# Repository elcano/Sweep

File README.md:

# Sweep
Lidar data collection from Scanse Sweep

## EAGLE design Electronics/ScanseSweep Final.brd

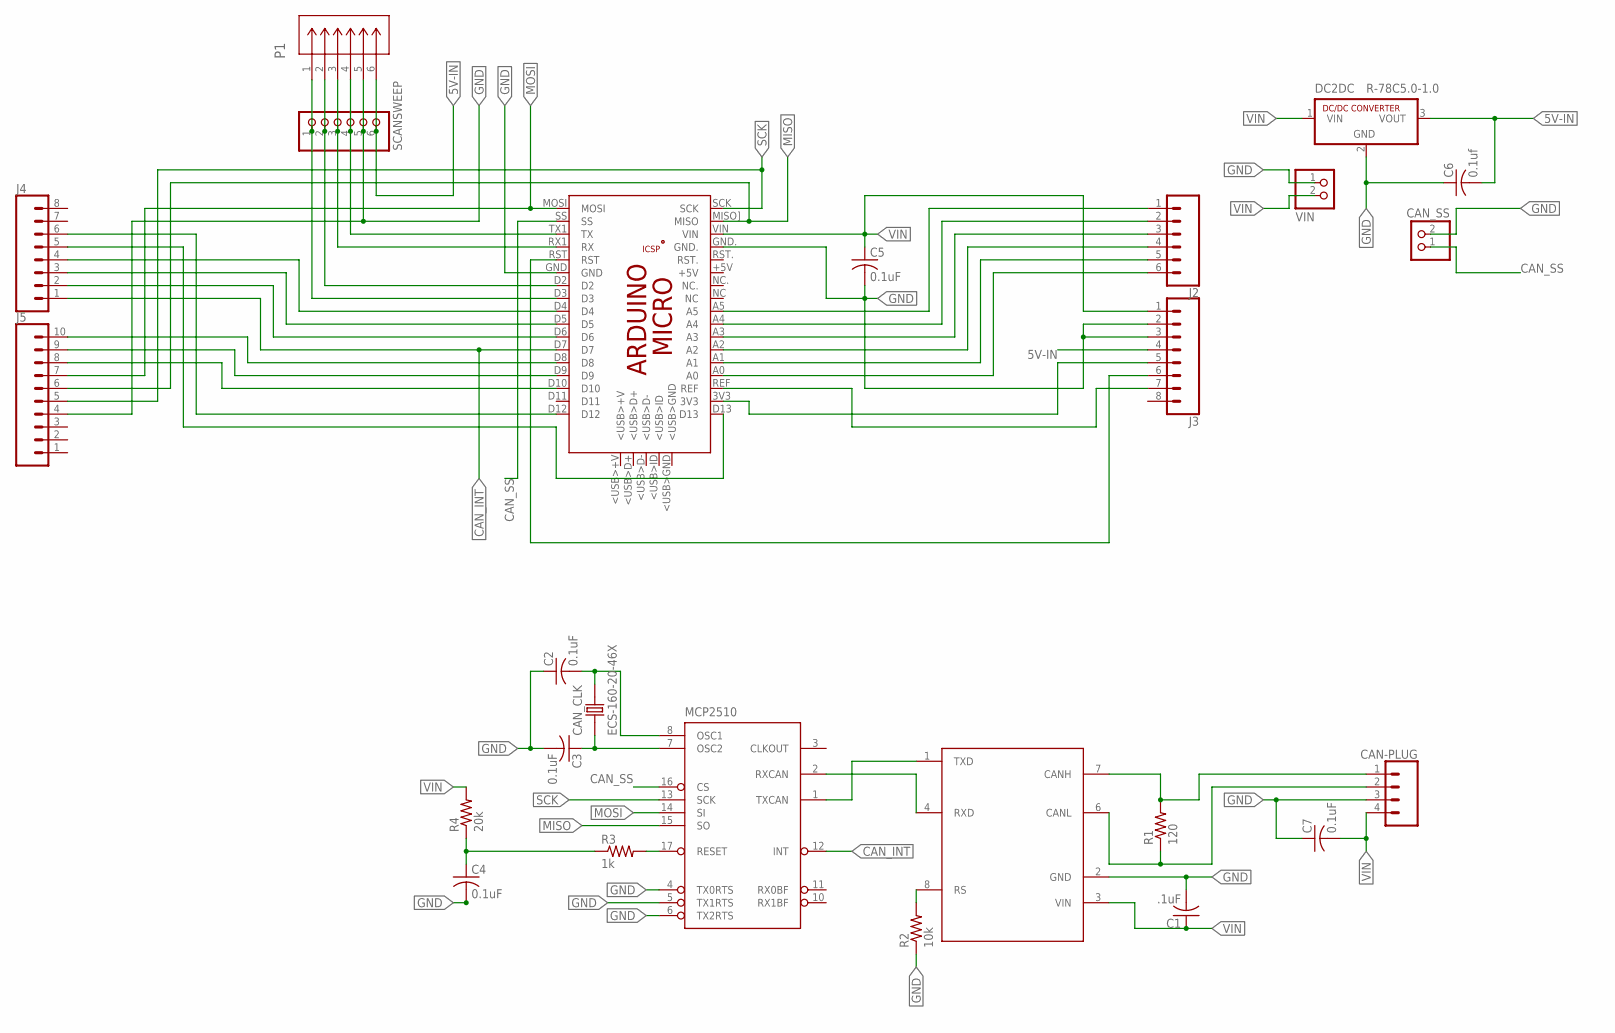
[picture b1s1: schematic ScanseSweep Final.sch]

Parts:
C1: .1uF; C025-024X044
C2, C3, C4, C5, C7: 0.1uF; C025-024X044
C6: 0.1uf; C025-024X044
CAN_CLK: ECS-160-20-46X; XTAL_ECS-160-20-46X
CAN_SS_TEST: CAN_SS; 1X02
DC2DC: R-78C5.0-1.0; SIP3
J1: CAN-PLUG; SCREWTERMINAL-3.5MM-4
J2: CONN_06SILK_FEMALE_PTH; 1X06
J3, J4: CONN_08"; 1X08
J5: CONN_10"; 1X10
MCP2510: MCP2510P; DIL18
MCP2551: MCP2551MCP2551; DIL08
P1: S6B-ZR(LF)(SN); S6B-ZR
PCB2: ARDUINO_MICRO
R1: 120; 0204/5
R2: 10k; 0204/5
R3: 1k; 0204/5
R4: 20k; 0204/5
SCANSESWEEP: SCANSWEEP; 1X06
VIN_TEST: VIN; 1X02

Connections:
3.3V: J3.5, PCB2.3V3
5V-IN: C6.2, DC2DC.3 (VOUT), J3.4, P1.6, SCANSESWEEP.6
A0: J2.6, PCB2.A0
A1: J2.5, PCB2.A1
A2: J2.4, PCB2.A2
A3: J2.3, PCB2.A3
A4: J2.2, PCB2.A4
A5: J2.1, PCB2.A5
CANH: J1.1, MCP2551.7 (CANH), R1.2
CANL: J1.2, MCP2551.6 (CANL), R1.1
CAN_INT: J4.1, MCP2510.12 (INT), PCB2.D7
CAN_SS: CAN_SS_TEST.1, MCP2510.16 (CS), PCB2.SS
D2: P1.2, PCB2.D2, SCANSESWEEP.2
D3: P1.1, PCB2.D3, SCANSESWEEP.1
D4: J4.4, PCB2.D4
D5: J4.3, PCB2.D5
D6: J4.2, PCB2.D6
D8: J5.10, PCB2.D8
D9: J5.9, PCB2.D9
D10: J5.8, PCB2.D10
D12: J4.6, PCB2.D12
D13: J4.5, PCB2.D13
GND: C1.2, C2.1, C3.2, C4.2, C5.2, C6.1, C7.1, CAN_SS_TEST.2, DC2DC.2 (GND), J1.3, J3.2, J3.3, J5.4, MCP2510.4 (TX0RTS), MCP2510.5 (TX1RTS), MCP2510.6 (TX2RTS), MCP2551.2 (GND), P1.5, PCB2.GND, PCB2.GND., R2.1, SCANSESWEEP.5, VIN_TEST.1
MISO: J5.6, MCP2510.15 (SO), PCB2.MISO] (MISO)
MOSI: J5.7, MCP2510.14 (SI), PCB2.MOSI
unnamed: C4.1, R3.1, R4.1
OSC1: C2.2, CAN_CLK.2, MCP2510.8 (OSC1)
OSC2: C3.1, CAN_CLK.1, MCP2510.7 (OSC2)
REF: J3.7, PCB2.REF
RESET: MCP2510.17 (RESET), R3.2
RS: MCP2551.8 (RS), R2.2
RST: J3.6, PCB2.RST
RX: P1.3, PCB2.RX1 (RX), SCANSESWEEP.3
RXCAN: MCP2510.2 (RXCAN), MCP2551.4 (RXD)
SCK: J5.5, MCP2510.13 (SCK), PCB2.SCK
TX: P1.4, PCB2.TX1 (TX), SCANSESWEEP.4
TXCAN: MCP2510.1 (TXCAN), MCP2551.1 (TXD)
VIN: C1.1, C5.1, C7.2, DC2DC.1 (VIN), J1.4, J3.1, MCP2551.3 (VIN), PCB2.VIN, R4.2, VIN_TEST.2

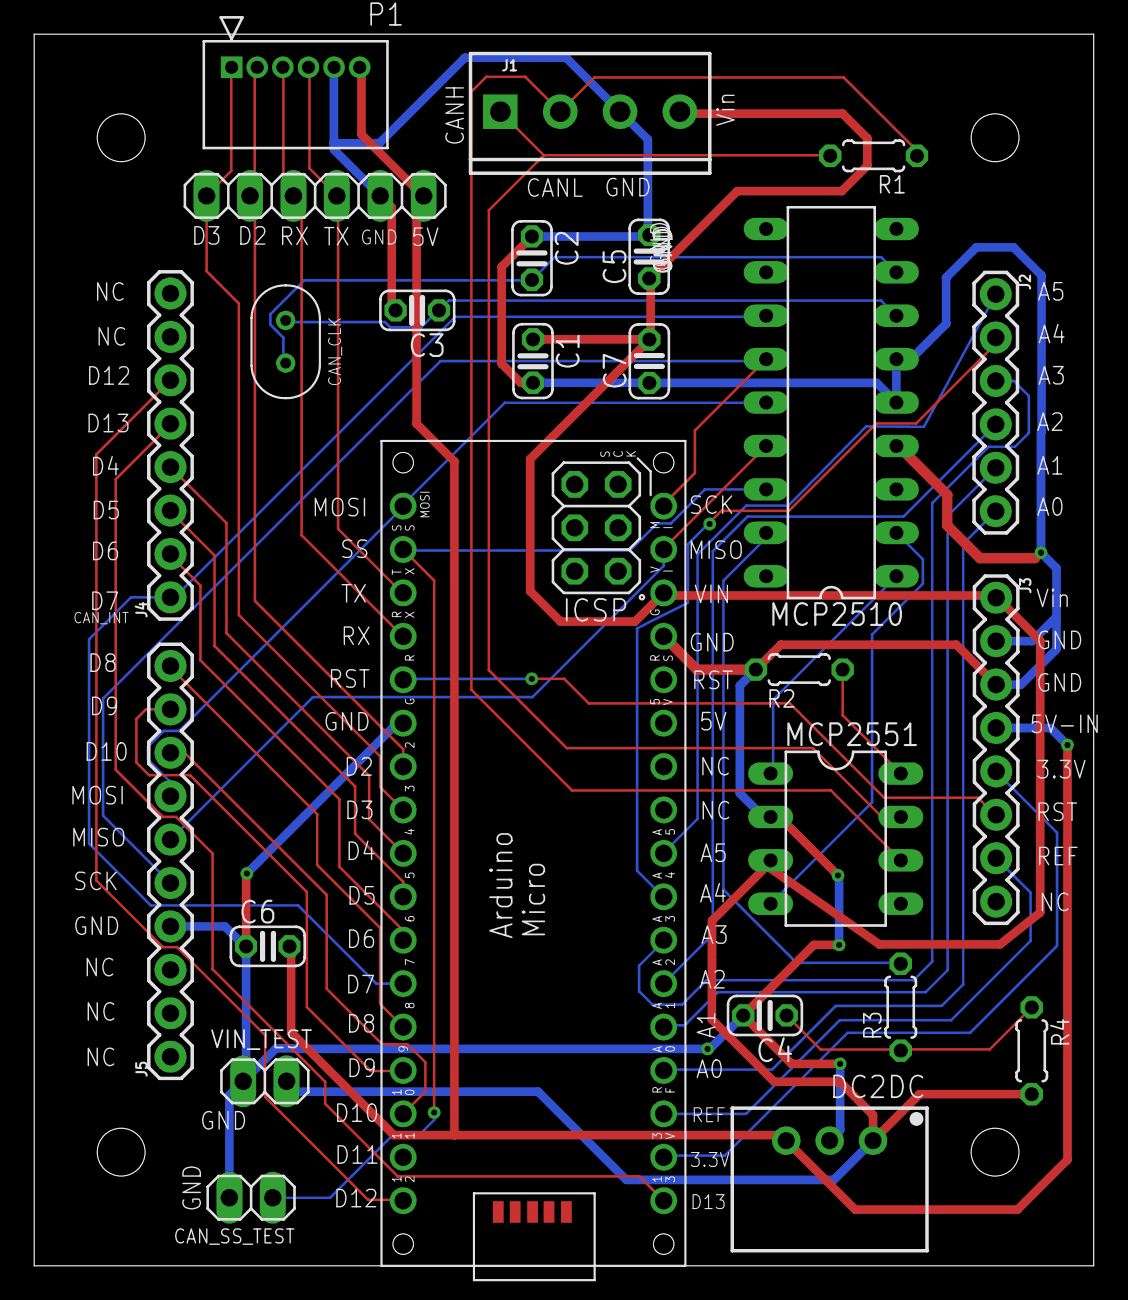
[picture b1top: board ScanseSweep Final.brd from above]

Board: 2 copper layers, 62.0 x 72.1 mm, 25 parts (0 on the bottom side), 38 nets.

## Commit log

2019-12-10 Mitchell Dean's Sweep Code
2019-12-10 Files for CAN bus
    CAN files should eventually be moved to Elcano/General.
    Sweep code needs to be modified to call the CAN routines.
2019-12-10 Modifications needed to PCB
    Basis for building the next version

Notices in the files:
parts and their libraries:
SparkFun-Connectors: Licensing: Creative Commons ShareAlike 4.0 International - https://creativecommons.org/licenses/by-sa/4.0
